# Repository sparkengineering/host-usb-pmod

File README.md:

# host-usb-pmod

[![View with - KiCanvas](https://img.shields.io/badge/KiCanvas-b187ff?label=View%20with
)](https://kicanvas.org/?github=https%3A%2F%2Fgithub.com%2Fsparkengineering%2Fhost-usb-pmod)

## Description

USB type A receptacle to Digilent Pmod™ breakout board.

- Impedance matched & length tuned differential lines
- Includes 3.3V to 5V boost converter (max. 800mA)
- Pinout to match Digilent high-speed Pmod™ e.g. on Arty A7
- Tested with Arty A7 board and USB 1.0 LS HID devices

## Contents

| File                                                 | Description             |
|------------------------------------------------------|-------------------------|
| [host-usb-pmod.pdf](./host-usb-pmod.pdf)             | Schematic in PDF format |
| [host-usb-pmod.csv](./host-usb-pmod.csv)             | BOM in CSV format       |
| [host-usb-pmod.png](./host-usb-pmod.png)             | PCB 3D render           |
|                                                      |                         |
| [host-usb-pmod.kicad_pro](./host-usb-pmod.kicad_pro) | KiCad 8.0.0 project     |
| [host-usb-pmod.kicad_pcb](./host-usb-pmod.kicad_pcb) | KiCad 8.0.0 PCB         |
| [host-usb-pmod.kicad_sch](./host-usb-pmod.kicad_sch) | KiCad 8.0.0 schematic   |

## Further Reading

- Ben Eater: How does a USB keyboard work? [^1]
- Compact USB HID host FPGA core [^2]
- A dual-socket USB host PMOD module [^3]
- Universal Serial Bus Specification 1.0 [^4]
- USB Host Dual Socket Pmod™ Compatible Module [^5]

[^1]: https://www.youtube.com/watch?v=wdgULBpRoXk
[^2]: https://github.com/nand2mario/usb_hid_host
[^3]: https://github.com/nand2mario/usb_host_pmod
[^4]: https://fabiensanglard.net/usbcheat/usb1.pdf
[^5]: https://machdyne.com/product/usb-host-dual-socket-pmod/

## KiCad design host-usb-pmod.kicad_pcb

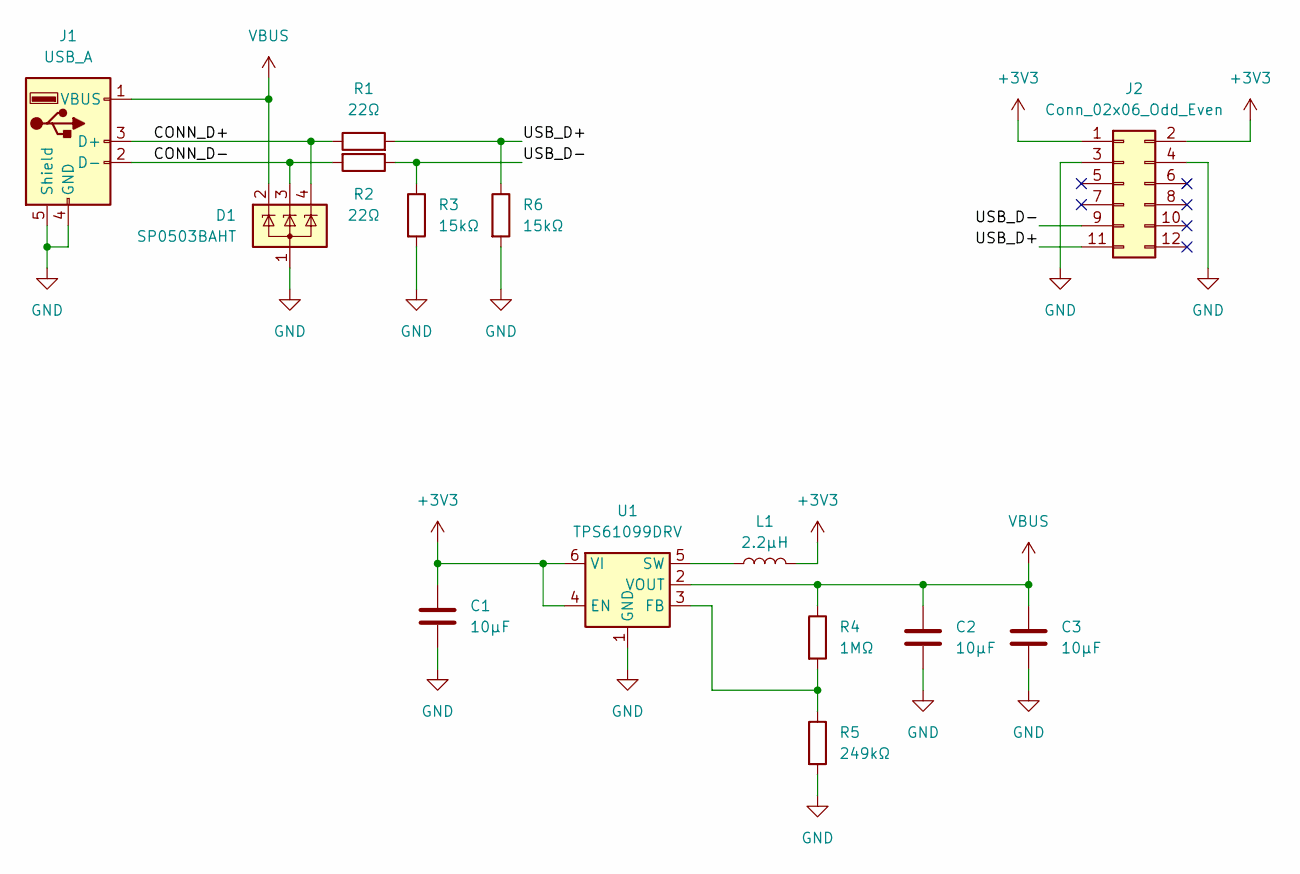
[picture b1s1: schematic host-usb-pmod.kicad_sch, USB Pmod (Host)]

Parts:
C1, C2, C3: 10µF; C_0603_1608Metric; MPN GRM188Z71A106KA73D
D1: SP0503BAHT; SOT-143; MPN SP0503BAHTG
J1: USB_A; USB_A_TE_292303-7_Horizontal; MPN 292303-7
J2: Conn_02x06_Odd_Even; PinHeader_2x06_P2.54mm_Horizontal; MPN 826634-6
L1: 2.2µH; L_Wurth_WE-LQSH-2512; MPN 74404024022
R1, R2: 22Ω; R_0402_1005Metric; MPN RC0402FR-0722RL
R3, R6: 15kΩ; R_0402_1005Metric; MPN RC0402FR-0715KL
R4: 1MΩ; R_0402_1005Metric; MPN RC0402FR-071ML
R5: 249kΩ; R_0402_1005Metric; MPN RC0402FR-07249KL
U1: TPS61099DRV; WSON-6-1EP_2x2mm_P0.65mm_EP1x1.6mm; MPN TPS61099DRVR

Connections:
+3V3: C1.1, J2.1, J2.2, L1.2, U1.4 (EN), U1.6 (VI)
/CONN_D+: D1.4 (K), J1.3 (D+), R1.1
/CONN_D-: D1.3 (K), J1.2 (D-), R2.2
/USB_D+: J2.11, R1.2, R6.1
/USB_D-: J2.9, R2.1, R3.1
GND: C1.2, C2.2, C3.2, D1.1 (A), J1.4 (GND), J1.5 (Shield), J2.3, J2.4, R3.2, R5.2, R6.2, U1.1 (GND), U1.7 (GND)
unnamed: R4.2, R5.1, U1.3 (FB)
unnamed: L1.1, U1.5 (SW)
VBUS: C2.1, C3.1, D1.2 (K), J1.1 (VBUS), R4.1, U1.2 (VOUT)

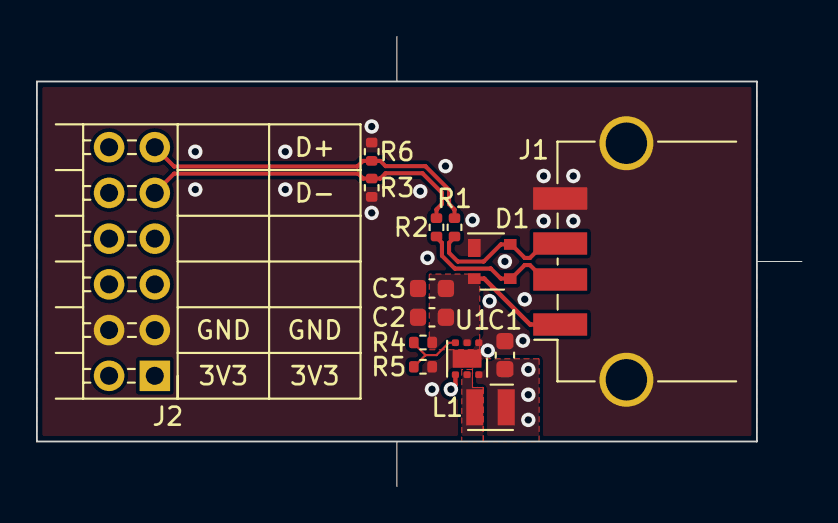
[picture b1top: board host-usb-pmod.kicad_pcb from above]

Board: 4 copper layers, 42.5 x 25.0 mm, 14 parts (0 on the bottom side), 9 nets.
